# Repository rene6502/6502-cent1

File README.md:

# 6502-cent1
A single board computer based on the W65C02S CPU.

## Features
- W65C02S running at 1 MHz
- 32K EEPROM
- 32K SRAM
- 2x VIA W65C22
- ACIA W65C51N
- Serial interface via RS232 DB9 or via USB
- Option to power via USB
- Minimal monitor with xmodem upload

## Demo
[This](examples/running_light.mp4) video shows the system in action.

## Schematics and PCB
- [PDF](kicad/schematics.pdf) of schematics
- See the KiCad project in folder [kicad](./kicad)  

## Jumpers
| JP1 | Function                                                      |
| --- | ------------------------------------------------------------- |
| Ext | powered from an external power supply (9V DC) connected to J1 |
| USB | powered from USB port                                         |

| JP2 + JP3 | Function                                          |
| --------- | ------------------------------------------------- |
| RS232     | serial connection via classic RS232 DB9 connector |
| USB       | serial connection via USB port *)                 |

*) The USB port implements a standard USB-to-Serial device.  
   It is based on the chip MCP2221 from Microchip Technology and works out of the box with Windows 10/11 and Linux.

## Connectors

## Software
All assembly programs must be built with [64tass](https://sourceforge.net/projects/tass64).

### Examples
- [running_light](./examples/running_light.asm)  
  outputs cyclic pattern on all VIA ports  
  see [video](examples/running_light.mp4)

- [acia_echo](./examples/acia_echo.asm)  
  echoes received character on serial port

### Enhanced BASIC  
downloads and patches source code with  [this](basic/build.sh) script

### Monitor
Simple [monitor](monitor/monitor.asm) program to upload and run a program using xmodem protocol.  

## Memory Map
| Address    | Device               |
| ---------- | -------------------- |
| $0000-7eff | RAM                  |
| $7f00-7f0f | VIA0                 |
| $7f10-7f1f | VIA1                 |
| $7f20-7f2f | ACIA                 |
| $7f30-7f3f | EXT (expansion port) |
| $7f40-7fff | unused               |
| $8000-ffff | ROM                  |

## Credits
Thanks to Ben Eater’s inspirational [videos](https://www.youtube.com/c/BenEater) and the work published by [Daryl Rictor](https://sbc.rictor.org).

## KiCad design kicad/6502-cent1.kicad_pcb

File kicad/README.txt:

https://github.com/Alarm-Siren/6502-kicad-library

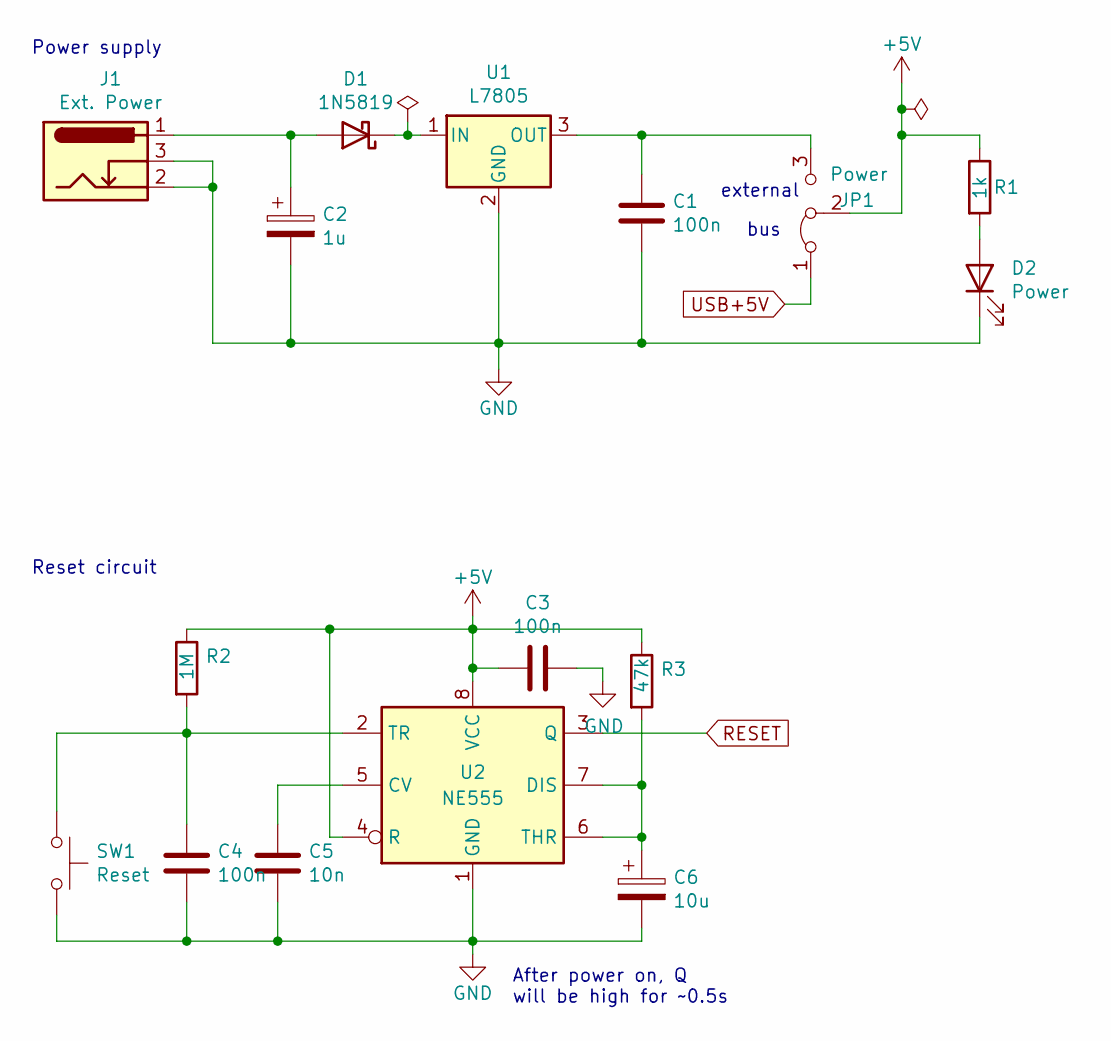
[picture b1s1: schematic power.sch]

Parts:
C1, C3, C4: 100n; C_Disc_D5.0mm_W2.5mm_P5.00mm
C2: 1u; CP_Radial_D5.0mm_P2.00mm
C5: 10n; C_Disc_D5.0mm_W2.5mm_P5.00mm
C6: 10u; CP_Radial_D5.0mm_P2.00mm
D1: 1N5819; D_DO-15_P10.16mm_Horizontal
D2: Power; LED_D5.0mm
J1: Ext. Power; BarrelJack_Horizontal
JP1: Power; PinHeader_1x03_P2.54mm_Vertical
R1: 1k; R_Axial_DIN0207_L6.3mm_D2.5mm_P10.16mm_Horizontal
R2: 1M; R_Axial_DIN0207_L6.3mm_D2.5mm_P10.16mm_Horizontal
R3: 47k; R_Axial_DIN0207_L6.3mm_D2.5mm_P10.16mm_Horizontal
SW1: Reset; SW_PUSH_6mm_H4.3mm
U1: L7805; TO-220-3_Horizontal_TabDown
U2: NE555; DIP-8_W7.62mm_Socket_LongPads

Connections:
+5V: C3.2, JP1.2 (C), R1.1, R2.1, R3.1, U2.4 (R), U2.8 (VCC); also elsewhere on the board
GND: C1.2, C2.2, C3.1, C4.2, C5.2, C6.2, D2.1 (K), J1.2, J1.3, SW1.2, U1.2 (GND), U2.1 (GND); also elsewhere on the board
unnamed: C1.1, JP1.3 (B), U1.3 (OUT)
unnamed: C2.1, D1.2 (A), J1.1
unnamed: C4.1, R2.2, SW1.1, U2.2 (TR)
unnamed: C5.1, U2.5 (CV)
unnamed: C6.1, R3.2, U2.6 (THR), U2.7 (DIS)
unnamed: D1.1 (K), U1.1 (IN)
unnamed: D2.2 (A), R1.2
RESET: U2.3 (Q); also elsewhere on the board
USB+5V: JP1.1 (A); also elsewhere on the board

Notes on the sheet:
Power supply
Reset circuit
After power on, Q will be high for ~~0.5s
bus
external

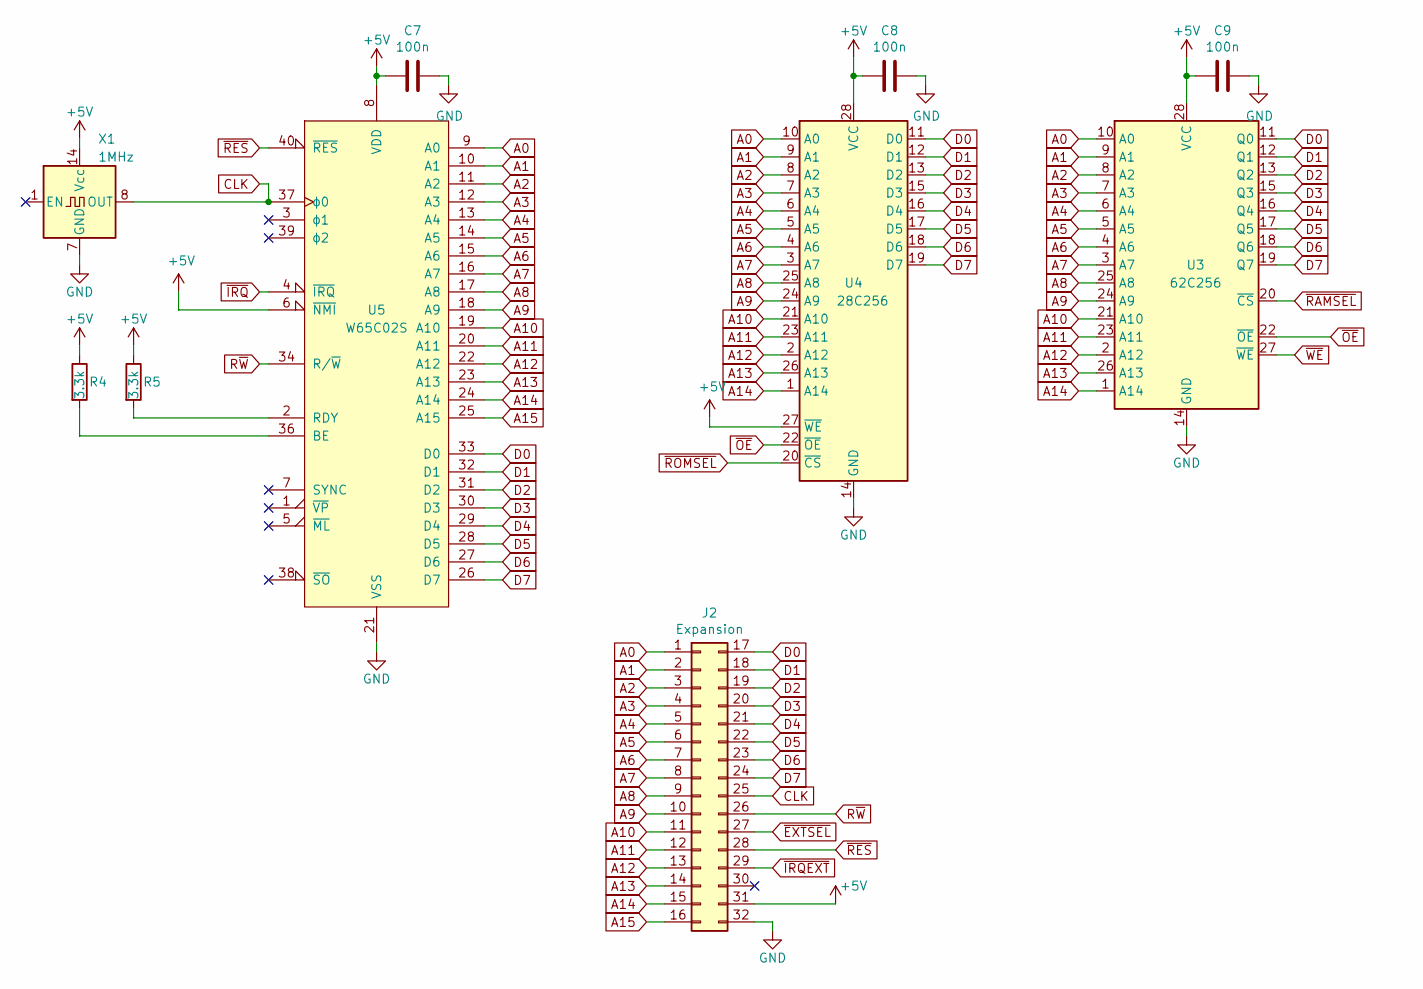
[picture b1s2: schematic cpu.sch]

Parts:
C7, C8, C9: 100n; C_Disc_D5.0mm_W2.5mm_P5.00mm
J2: Expansion; PinSocket_2x16_P2.54mm_Vertical
R4, R5: 3.3k; R_Axial_DIN0207_L6.3mm_D2.5mm_P10.16mm_Horizontal
U3: 62C256; DIP-28_W15.24mm_Socket_LongPads
U4: 28C256; DIP_Socket-28_W11.9_W12.7_W15.24_W17.78_W18.5_3M_228-1277-0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
U5: W65C02S; DIP-40_W15.24mm_Socket_LongPads
X1: 1MHz; DIP-14_W7.62mm_Socket_LongPads

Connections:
+5V: C7.2, C8.2, C9.2, J2.31, R4.1, R5.1, U3.28 (VCC), U4.27 (~WE), U4.28 (VCC), U5.6 (~NMI), U5.8 (VDD), X1.14 (Vcc); also elsewhere on the board
A0: J2.1, U3.10 (A0), U4.10 (A0), U5.9 (A0); also elsewhere on the board
A1: J2.2, U3.9 (A1), U4.9 (A1), U5.10 (A1); also elsewhere on the board
A2: J2.3, U3.8 (A2), U4.8 (A2), U5.11 (A2); also elsewhere on the board
A3: J2.4, U3.7 (A3), U4.7 (A3), U5.12 (A3); also elsewhere on the board
A4: J2.5, U3.6 (A4), U4.6 (A4), U5.13 (A4); also elsewhere on the board
A5: J2.6, U3.5 (A5), U4.5 (A5), U5.14 (A5); also elsewhere on the board
A6: J2.7, U3.4 (A6), U4.4 (A6), U5.15 (A6); also elsewhere on the board
A7: J2.8, U3.3 (A7), U4.3 (A7), U5.16 (A7); also elsewhere on the board
A8: J2.9, U3.25 (A8), U4.25 (A8), U5.17 (A8); also elsewhere on the board
A9: J2.10, U3.24 (A9), U4.24 (A9), U5.18 (A9); also elsewhere on the board
A10: J2.11, U3.21 (A10), U4.21 (A10), U5.19 (A10); also elsewhere on the board
A11: J2.12, U3.23 (A11), U4.23 (A11), U5.20 (A11); also elsewhere on the board
A12: J2.13, U3.2 (A12), U4.2 (A12), U5.22 (A12); also elsewhere on the board
A13: J2.14, U3.26 (A13), U4.26 (A13), U5.23 (A13); also elsewhere on the board
A14: J2.15, U3.1 (A14), U4.1 (A14), U5.24 (A14); also elsewhere on the board
A15: J2.16, U5.25 (A15); also elsewhere on the board
CLK: J2.25, U5.37 (ϕ0), X1.8 (OUT); also elsewhere on the board
D0: J2.17, U3.11 (Q0), U4.11 (D0), U5.33 (D0); also elsewhere on the board
D1: J2.18, U3.12 (Q1), U4.12 (D1), U5.32 (D1); also elsewhere on the board
D2: J2.19, U3.13 (Q2), U4.13 (D2), U5.31 (D2); also elsewhere on the board
D3: J2.20, U3.15 (Q3), U4.15 (D3), U5.30 (D3); also elsewhere on the board
D4: J2.21, U3.16 (Q4), U4.16 (D4), U5.29 (D4); also elsewhere on the board
D5: J2.22, U3.17 (Q5), U4.17 (D5), U5.28 (D5); also elsewhere on the board
D6: J2.23, U3.18 (Q6), U4.18 (D6), U5.27 (D6); also elsewhere on the board
D7: J2.24, U3.19 (Q7), U4.19 (D7), U5.26 (D7); also elsewhere on the board
GND: C7.1, C8.1, C9.1, J2.32, U3.14 (GND), U4.14 (GND), U5.21 (VSS), X1.7 (GND); also elsewhere on the board
unnamed: R4.2, U5.36 (BE)
unnamed: R5.2, U5.2 (RDY)
R~W: J2.26, U5.34 (R/~W); also elsewhere on the board
~EXTSEL: J2.27; also elsewhere on the board
~IRQ: U5.4 (~IRQ); also elsewhere on the board
~IRQEXT: J2.29; also elsewhere on the board
~OE: U3.22 (~OE), U4.22 (~OE); also elsewhere on the board
~RAMSEL: U3.20 (~CS); also elsewhere on the board
~RES: J2.28, U5.40 (~RES); also elsewhere on the board
~ROMSEL: U4.20 (~CS); also elsewhere on the board
~WE: U3.27 (~WE); also elsewhere on the board

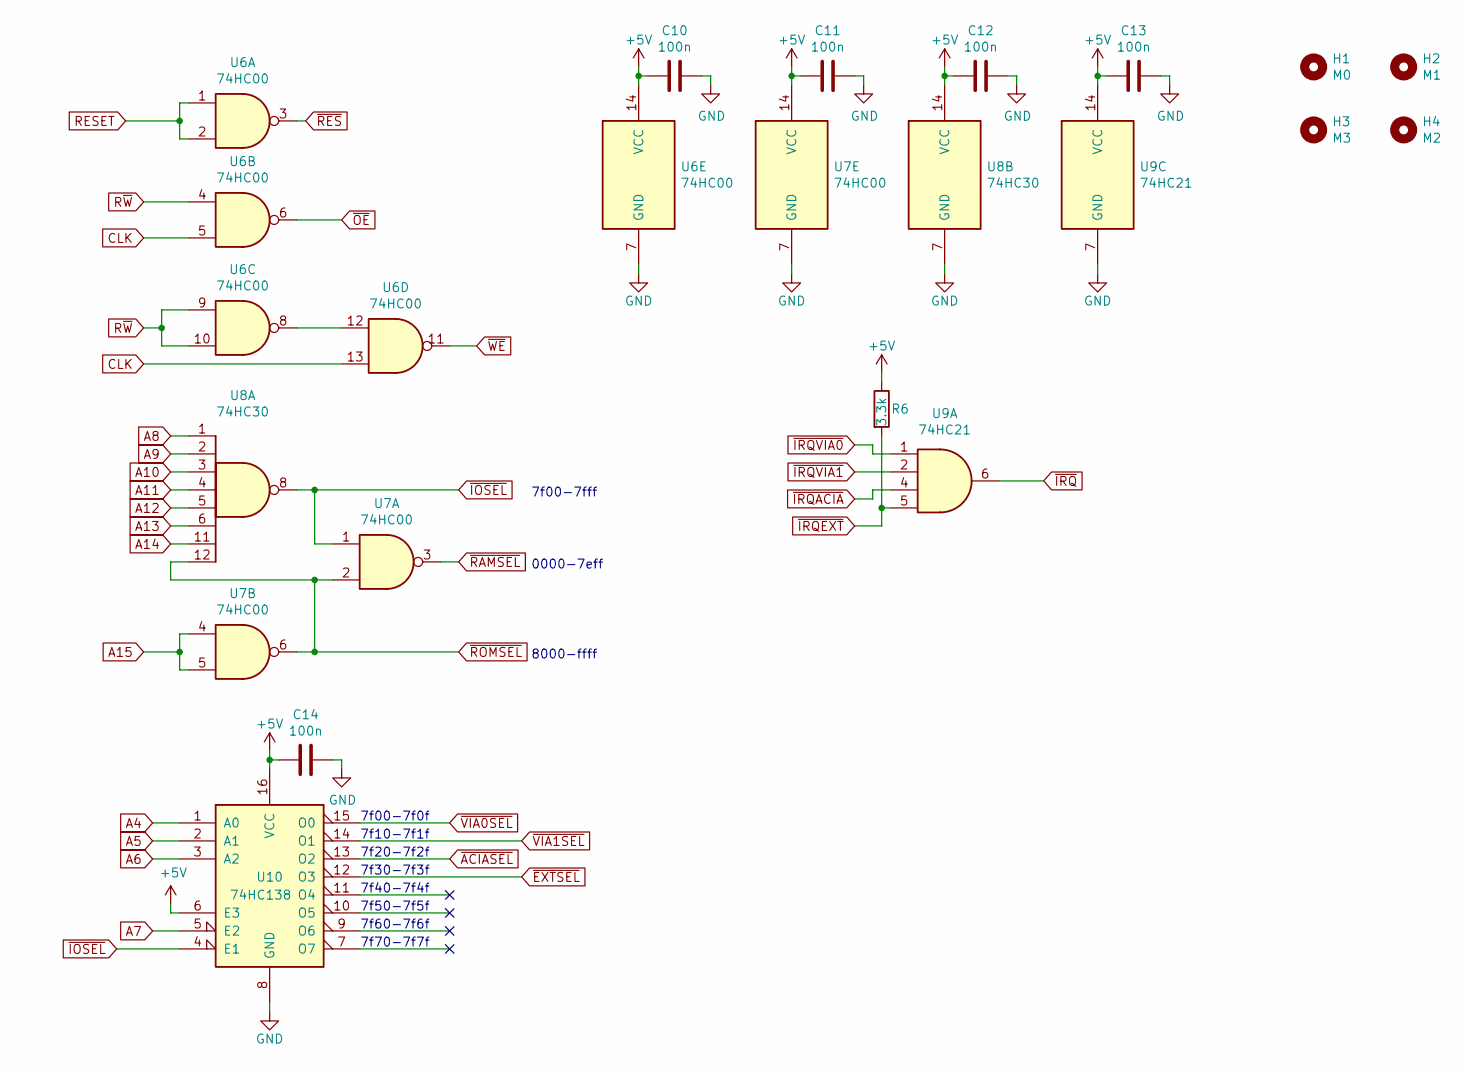
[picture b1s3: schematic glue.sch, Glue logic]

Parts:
C10, C11, C12, C13, C14: 100n; C_Disc_D5.0mm_W2.5mm_P5.00mm
H1: M0; MountingHole_3.2mm_M3_Pad_Via
H2: M1; MountingHole_3.2mm_M3_Pad_Via
H3: M3; MountingHole_3.2mm_M3_Pad_Via
H4: M2; MountingHole_3.2mm_M3_Pad_Via
R6: 3.3k; R_Axial_DIN0207_L6.3mm_D2.5mm_P10.16mm_Horizontal
U6, U7: 74HC00; DIP-14_W7.62mm_Socket_LongPads
U8: 74HC30; DIP-14_W7.62mm_Socket_LongPads
U9: 74HC21; DIP-14_W7.62mm_Socket_LongPads
U10: 74HC138; DIP-16_W7.62mm_Socket_LongPads

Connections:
+5V: C10.2, C11.2, C12.2, C13.2, C14.2, R6.1, U6.14 (VCC), U7.14 (VCC), U8.14 (VCC), U9.14 (VCC), U10.6 (E3), U10.16 (VCC); also elsewhere on the board
A4: U10.1 (A0); also elsewhere on the board
A5: U10.2 (A1); also elsewhere on the board
A6: U10.3 (A2); also elsewhere on the board
A7: U10.5 (E2); also elsewhere on the board
A8: U8.1; also elsewhere on the board
A9: U8.2; also elsewhere on the board
A10: U8.3; also elsewhere on the board
A11: U8.4; also elsewhere on the board
A12: U8.5; also elsewhere on the board
A13: U8.6; also elsewhere on the board
A14: U8.11; also elsewhere on the board
A15: U7.4, U7.5; also elsewhere on the board
CLK: U6.5, U6.13; also elsewhere on the board
GND: C10.1, C11.1, C12.1, C13.1, C14.1, U6.7 (GND), U7.7 (GND), U8.7 (GND), U9.7 (GND), U10.8 (GND); also elsewhere on the board
unnamed: U6.8, U6.12
RESET: U6.1, U6.2; also elsewhere on the board
R~W: U6.4, U6.9, U6.10; also elsewhere on the board
~ACIASEL: U10.13 (O2); also elsewhere on the board
~EXTSEL: U10.12 (O3); also elsewhere on the board
~IOSEL: U7.1, U8.8, U10.4 (E1)
~IRQ: U9.6; also elsewhere on the board
~IRQACIA: U9.4; also elsewhere on the board
~IRQEXT: R6.2, U9.5; also elsewhere on the board
~IRQVIA0: U9.1; also elsewhere on the board
~IRQVIA1: U9.2; also elsewhere on the board
~OE: U6.6; also elsewhere on the board
~RAMSEL: U7.3; also elsewhere on the board
~RES: U6.3; also elsewhere on the board
~ROMSEL: U7.2, U7.6, U8.12; also elsewhere on the board
~VIA0SEL: U10.15 (O0); also elsewhere on the board
~VIA1SEL: U10.14 (O1); also elsewhere on the board
~WE: U6.11; also elsewhere on the board

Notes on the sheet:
8000-ffff
7f00-7fff
0000-7eff
7f00-7f0f
7f10-7f1f
7f20-7f2f
7f30-7f3f
7f40-7f4f
7f50-7f5f
7f60-7f6f
7f70-7f7f

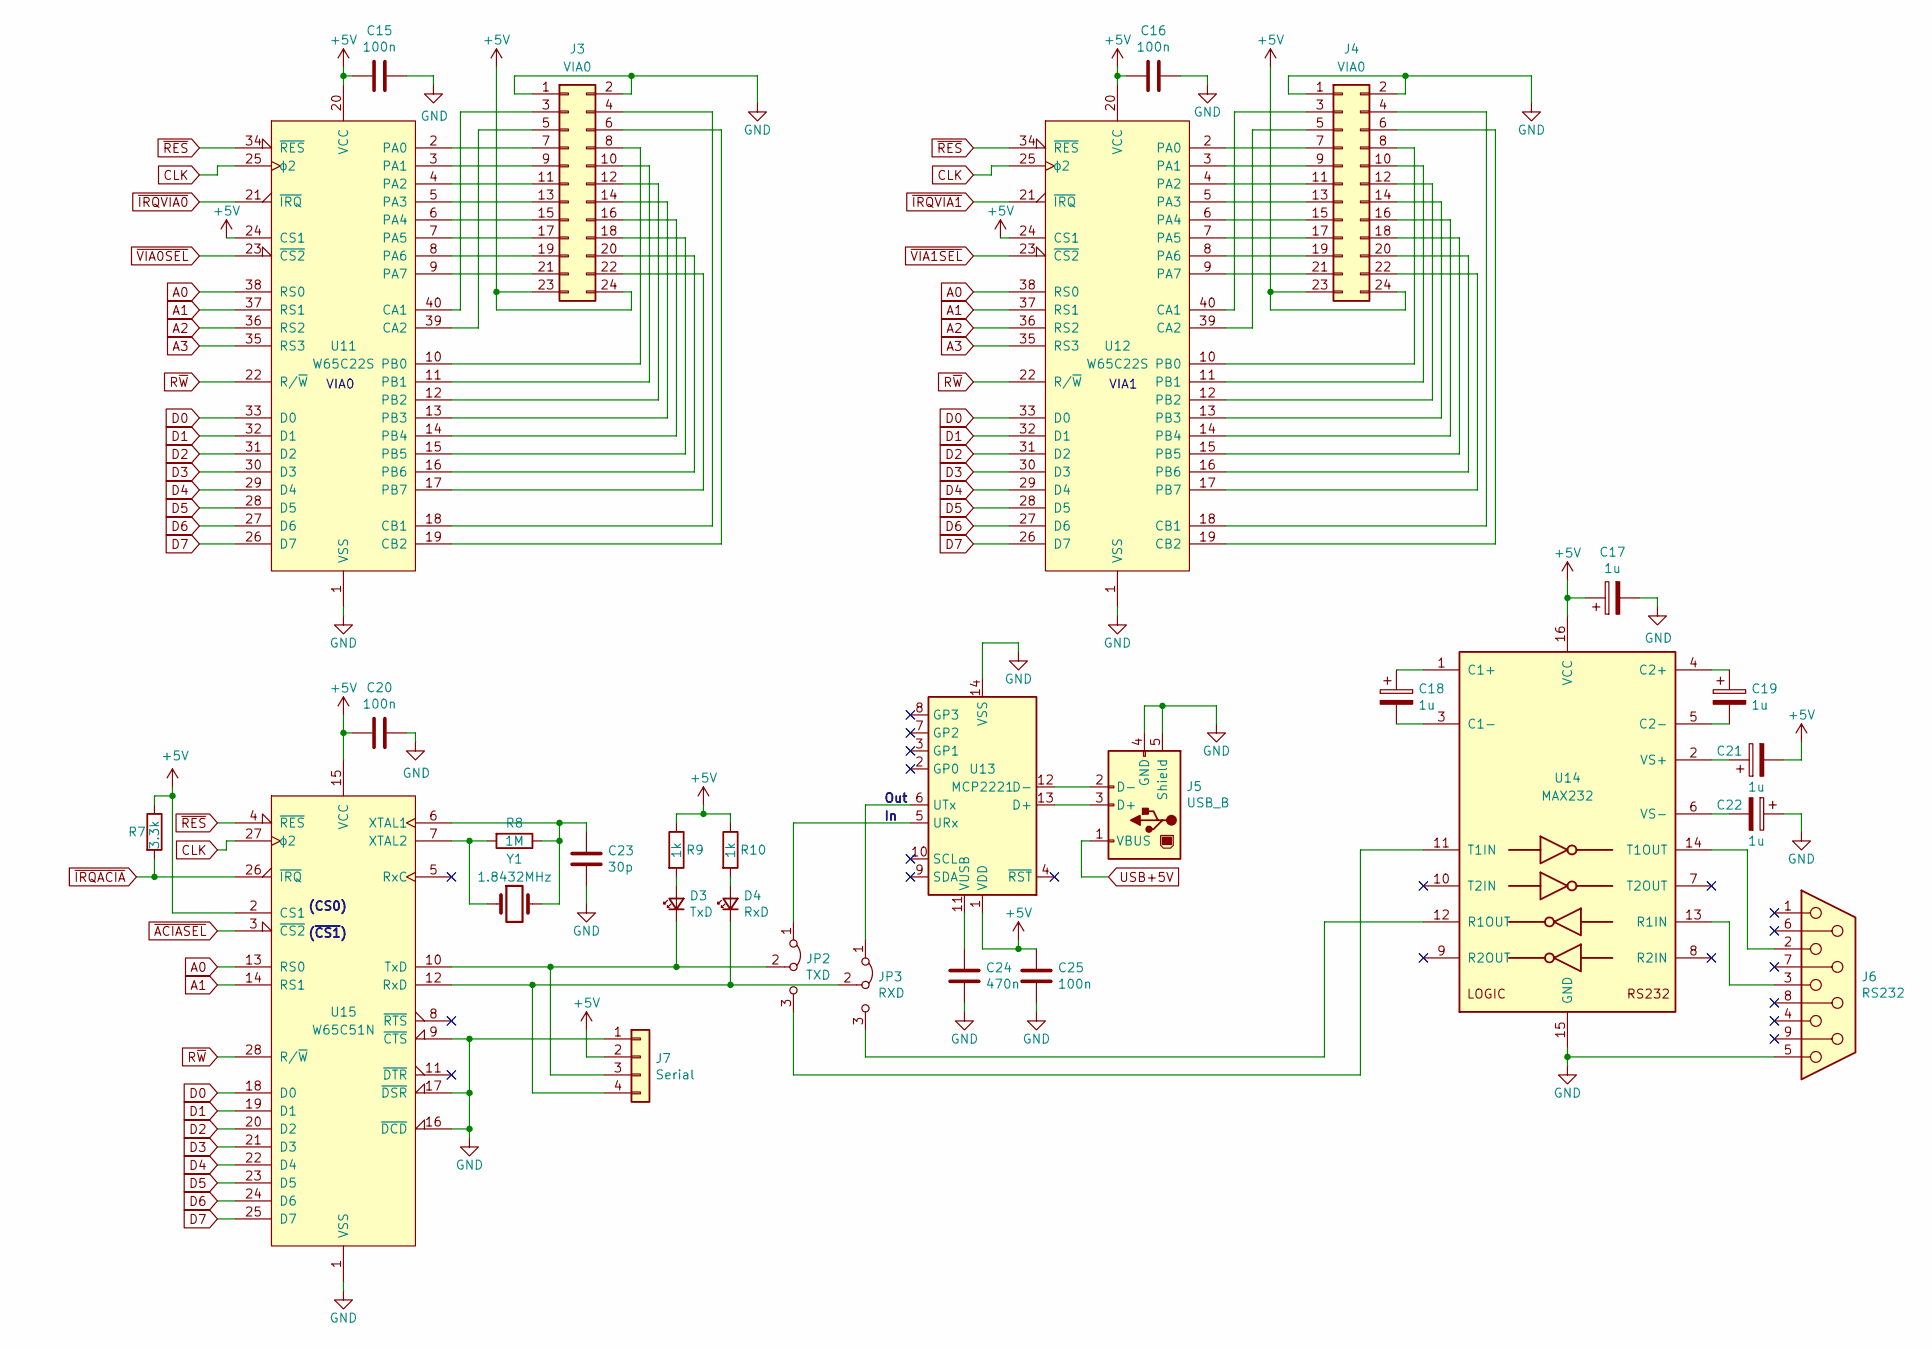
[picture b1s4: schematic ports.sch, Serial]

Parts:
C15, C16, C20, C25: 100n; C_Disc_D5.0mm_W2.5mm_P5.00mm
C17, C18, C19, C21, C22: 1u; CP_Radial_D5.0mm_P2.00mm
C23: 30p; C_Disc_D5.0mm_W2.5mm_P5.00mm
C24: 470n; C_Disc_D5.0mm_W2.5mm_P5.00mm
D3: TxD; LED_D5.0mm
D4: RxD; LED_D5.0mm
J3, J4: VIA0; PinSocket_2x12_P2.54mm_Vertical
J5: USB_B; USB_B_Lumberg_2411_02_Horizontal
J6: RS232; DSUB-9_Female_Horizontal_P2.77x2.84mm_EdgePinOffset7.70mm_H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
J7: Serial; PinSocket_1x04_P2.54mm_Vertical
JP2: TXD; PinHeader_1x03_P2.54mm_Vertical
JP3: RXD; PinHeader_1x03_P2.54mm_Vertical
R7: 3.3k; R_Axial_DIN0207_L6.3mm_D2.5mm_P10.16mm_Horizontal
R8: 1M; R_Axial_DIN0207_L6.3mm_D2.5mm_P10.16mm_Horizontal
R9, R10: 1k; R_Axial_DIN0207_L6.3mm_D2.5mm_P10.16mm_Horizontal
U11, U12: W65C22S; DIP-40_W15.24mm_Socket_LongPads
U13: MCP2221; DIP-14_W7.62mm_Socket_LongPads
U14: MAX232; DIP-16_W7.62mm_Socket_LongPads
U15: W65C51N; DIP-28_W15.24mm_Socket_LongPads
Y1: 1.8432MHz; Crystal_HC18-U_Vertical

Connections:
+5V: C15.2, C16.2, C17.1, C20.2, C21.2, C25.1, J3.23, J3.24, J4.23, J4.24, J7.2, R7.1, R9.1, R10.1, U11.20 (VCC), U11.24 (CS1), U12.20 (VCC), U12.24 (CS1), U13.1 (VDD), U14.16 (VCC), U15.2 (CS1), U15.15 (VCC); also elsewhere on the board
A0: U11.38 (RS0), U12.38 (RS0), U15.13 (RS0); also elsewhere on the board
A1: U11.37 (RS1), U12.37 (RS1), U15.14 (RS1); also elsewhere on the board
A2: U11.36 (RS2), U12.36 (RS2); also elsewhere on the board
A3: U11.35 (RS3), U12.35 (RS3); also elsewhere on the board
CLK: U11.25 (ϕ2), U12.25 (ϕ2), U15.27 (ϕ2); also elsewhere on the board
D0: U11.33 (D0), U12.33 (D0), U15.18 (D0); also elsewhere on the board
D1: U11.32 (D1), U12.32 (D1), U15.19 (D1); also elsewhere on the board
D2: U11.31 (D2), U12.31 (D2), U15.20 (D2); also elsewhere on the board
D3: U11.30 (D3), U12.30 (D3), U15.21 (D3); also elsewhere on the board
D4: U11.29 (D4), U12.29 (D4), U15.22 (D4); also elsewhere on the board
D5: U11.28 (D5), U12.28 (D5), U15.23 (D5); also elsewhere on the board
D6: U11.27 (D6), U12.27 (D6), U15.24 (D6); also elsewhere on the board
D7: U11.26 (D7), U12.26 (D7), U15.25 (D7); also elsewhere on the board
GND: C15.1, C16.1, C17.2, C20.1, C22.1, C23.2, C24.2, C25.2, J3.1, J3.2, J4.1, J4.2, J5.4 (GND), J5.5 (Shield), J6.5, J7.1, U11.1 (VSS), U12.1 (VSS), U13.14 (VSS), U14.15 (GND), U15.1 (VSS), U15.9 (~CTS), U15.16 (~DCD), U15.17 (~DSR); also elsewhere on the board
unnamed: C18.1, U14.1 (C1+)
unnamed: C18.2, U14.3 (C1-)
unnamed: C19.1, U14.4 (C2+)
unnamed: C19.2, U14.5 (C2-)
unnamed: C21.1, U14.2 (VS+)
unnamed: C22.2, U14.6 (VS-)
unnamed: C23.1, R8.1, U15.6 (XTAL1), Y1.2
unnamed: C24.1, U13.11 (VUSB)
unnamed: D3.1 (K), J7.3, JP2.2 (C), U15.10 (TxD)
unnamed: D3.2 (A), R9.2
unnamed: D4.1 (K), J7.4, JP3.2 (C), U15.12 (RxD)
unnamed: D4.2 (A), R10.2
unnamed: J3.3, U11.40 (CA1)
unnamed: J3.4, U11.18 (CB1)
unnamed: J3.5, U11.39 (CA2)
unnamed: J3.6, U11.19 (CB2)
unnamed: J3.7, U11.2 (PA0)
unnamed: J3.8, U11.10 (PB0)
unnamed: J3.9, U11.3 (PA1)
unnamed: J3.10, U11.11 (PB1)
unnamed: J3.11, U11.4 (PA2)
unnamed: J3.12, U11.12 (PB2)
unnamed: J3.13, U11.5 (PA3)
unnamed: J3.14, U11.13 (PB3)
unnamed: J3.15, U11.6 (PA4)
unnamed: J3.16, U11.14 (PB4)
unnamed: J3.17, U11.7 (PA5)
unnamed: J3.18, U11.15 (PB5)
unnamed: J3.19, U11.8 (PA6)
unnamed: J3.20, U11.16 (PB6)
unnamed: J3.21, U11.9 (PA7)
unnamed: J3.22, U11.17 (PB7)
unnamed: J4.3, U12.40 (CA1)
unnamed: J4.4, U12.18 (CB1)
unnamed: J4.5, U12.39 (CA2)
unnamed: J4.6, U12.19 (CB2)
unnamed: J4.7, U12.2 (PA0)
unnamed: J4.8, U12.10 (PB0)
unnamed: J4.9, U12.3 (PA1)
unnamed: J4.10, U12.11 (PB1)
unnamed: J4.11, U12.4 (PA2)
unnamed: J4.12, U12.12 (PB2)
unnamed: J4.13, U12.5 (PA3)
unnamed: J4.14, U12.13 (PB3)
unnamed: J4.15, U12.6 (PA4)
unnamed: J4.16, U12.14 (PB4)
unnamed: J4.17, U12.7 (PA5)
unnamed: J4.18, U12.15 (PB5)
unnamed: J4.19, U12.8 (PA6)
unnamed: J4.20, U12.16 (PB6)
unnamed: J4.21, U12.9 (PA7)
unnamed: J4.22, U12.17 (PB7)
unnamed: J5.2 (D-), U13.12 (D-)
unnamed: J5.3 (D+), U13.13 (D+)
unnamed: J6.2, U14.14 (T1OUT)
unnamed: J6.3, U14.13 (R1IN)
unnamed: JP2.1 (A), U13.5 (URx)
unnamed: JP2.3 (B), U14.11 (T1IN)
unnamed: JP3.1 (A), U13.6 (UTx)
unnamed: JP3.3 (B), U14.12 (R1OUT)
unnamed: R8.2, U15.7 (XTAL2), Y1.1
R~W: U11.22 (R/~W), U12.22 (R/~W), U15.28 (R/~W); also elsewhere on the board
USB+5V: J5.1 (VBUS); also elsewhere on the board
~ACIASEL: U15.3 (~CS2); also elsewhere on the board
~IRQACIA: R7.2, U15.26 (~IRQ); also elsewhere on the board
~IRQVIA0: U11.21 (~IRQ); also elsewhere on the board
~IRQVIA1: U12.21 (~IRQ); also elsewhere on the board
~RES: U11.34 (~RES), U12.34 (~RES), U15.4 (~RES); also elsewhere on the board
~VIA0SEL: U11.23 (~CS2); also elsewhere on the board
~VIA1SEL: U12.23 (~CS2); also elsewhere on the board

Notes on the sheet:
VIA0
VIA1
(CS0)
(~CS1)
Out

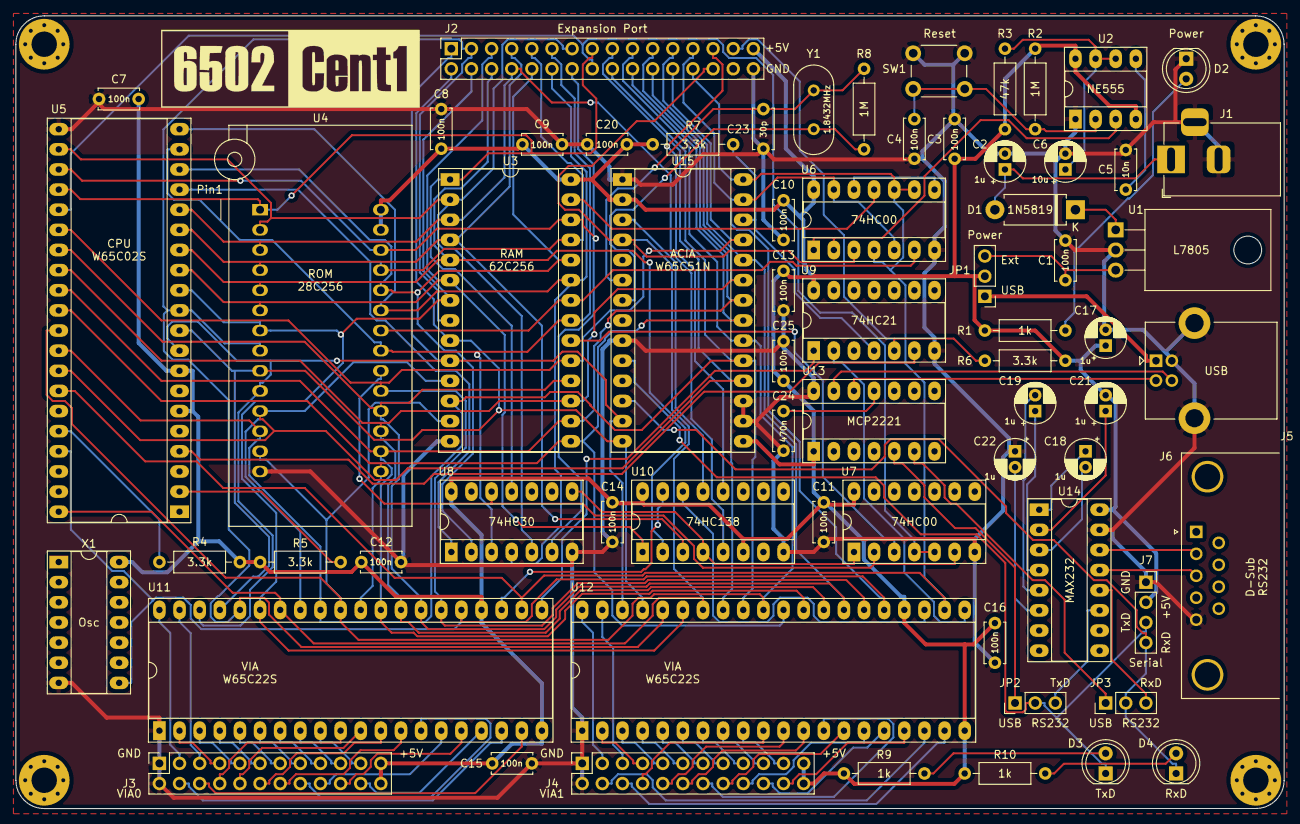
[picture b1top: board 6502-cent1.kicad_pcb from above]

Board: 2 copper layers, 160.0 x 100.0 mm, 71 parts (0 on the bottom side), 116 nets.

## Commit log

2021-12-24 fix and improve intel hex loader fix checksum calculation dont wait after sending ackn. ESC -> aborts download
2022-01-16 change file transfer protocol to xmodem
2022-02-10 fix typo
2022-03-08 initialize stack pointer
